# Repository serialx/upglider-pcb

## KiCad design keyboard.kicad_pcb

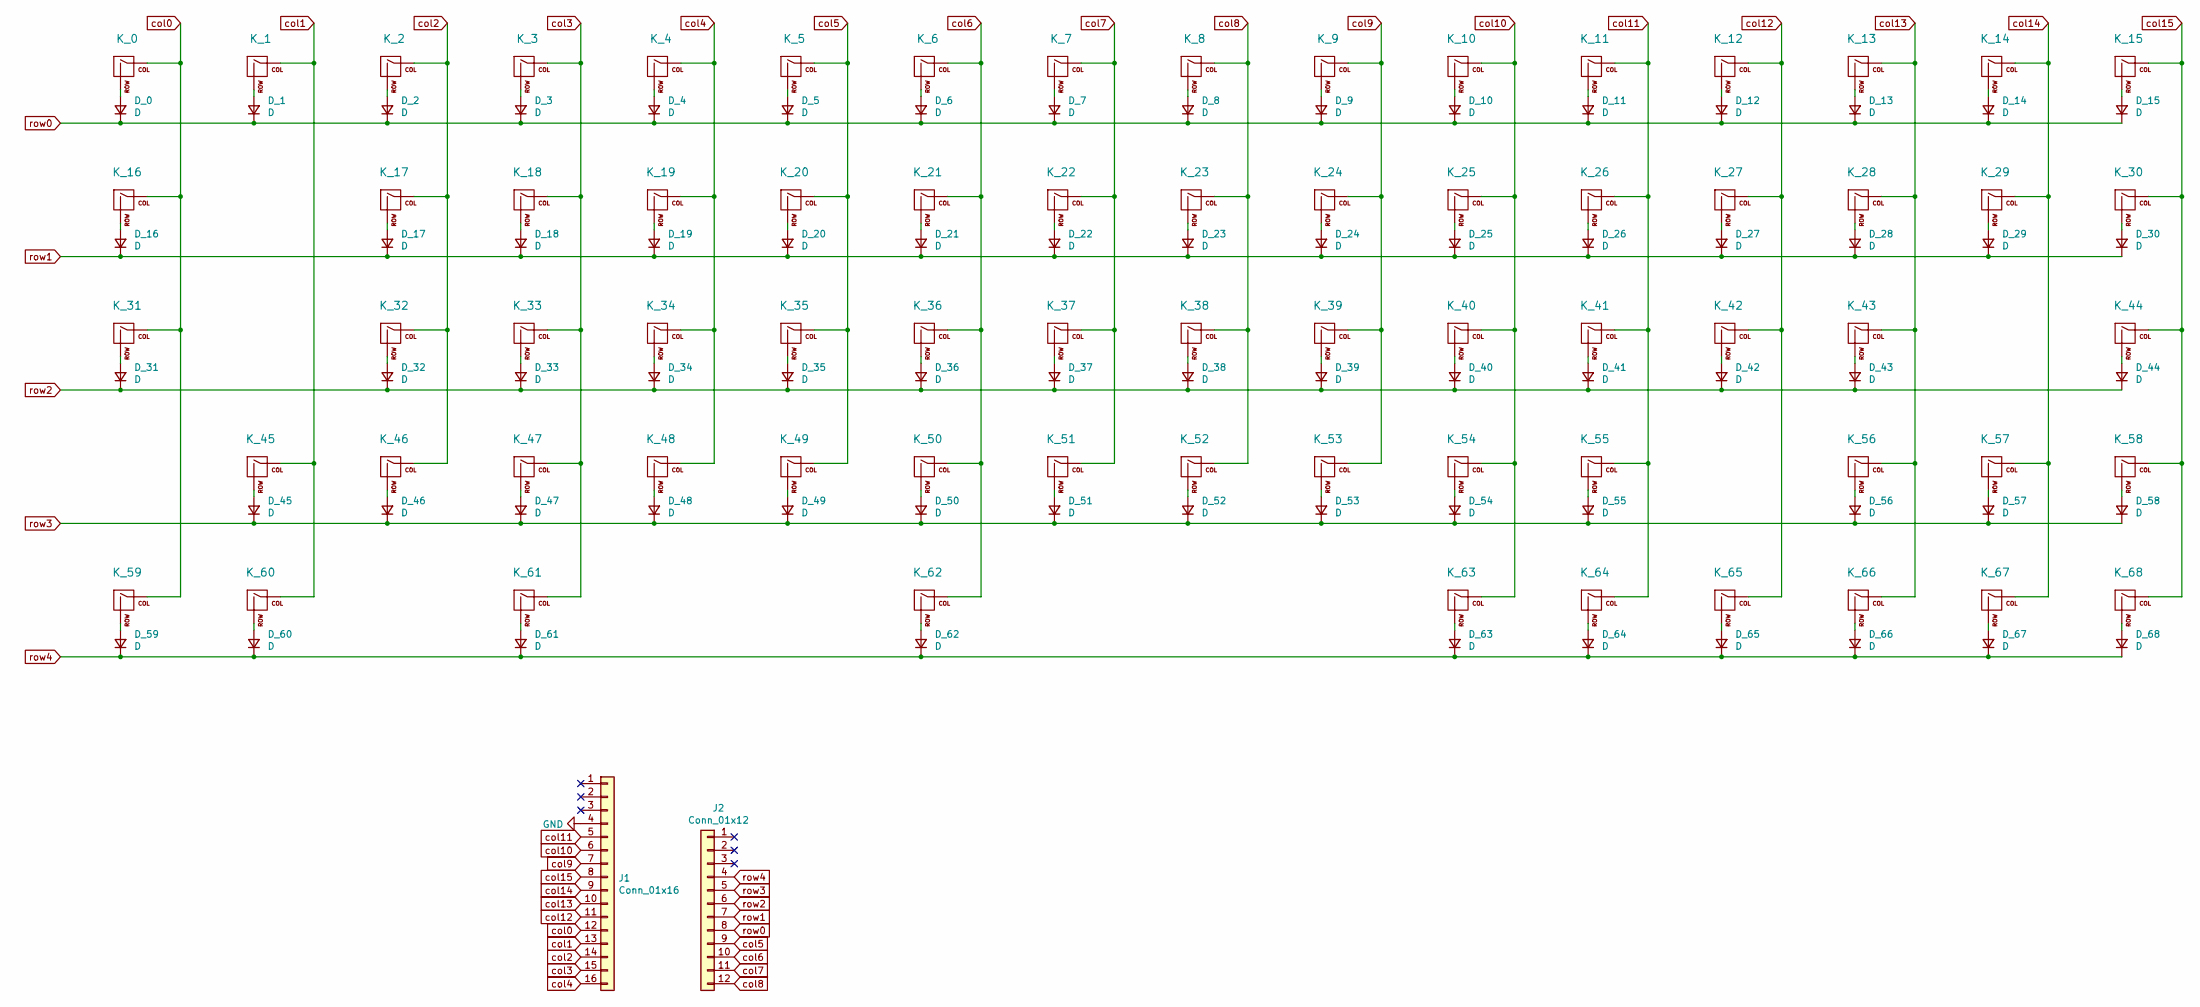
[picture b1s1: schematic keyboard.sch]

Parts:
D_0, D_1, D_2, D_3, D_4, D_5, D_6, D_7, D_8, D_9, D_10, D_11, D_12, D_13, D_14, D_15, D_16, D_17, D_18, D_19, D_20, D_21, D_22, D_23, D_24, D_25, D_26, D_27, D_28, D_29, D_30, D_31, D_32, D_33, D_34, D_35, D_36, D_37, D_38, D_39, D_40, D_41, D_42, D_43, D_44, D_45, D_46, D_47, D_48, D_49, D_50, D_51, D_52, D_53, D_54, D_55, D_56, D_57, D_58, D_59, D_60, D_61, D_62, D_63, D_64, D_65, D_66, D_67, D_68: D; D_SOD-123; LCSC Part # C81598
J1: Conn_01x16; PinSocket_1x16_P2.54mm_Vertical
J2: Conn_01x12; PinSocket_1x12_P2.54mm_Vertical
K_0, K_1, K_2, K_3, K_4, K_5, K_6, K_7, K_8, K_9, K_10, K_11, K_12, K_13, K_14, K_15, K_17, K_18, K_19, K_20, K_21, K_22, K_23, K_24, K_25, K_26, K_27, K_28, K_30, K_32, K_33, K_34, K_35, K_36, K_37, K_38, K_39, K_40, K_41, K_42, K_44, K_46, K_47, K_48, K_49, K_50, K_51, K_52, K_53, K_54, K_55, K_57, K_58, K_63, K_64, K_65, K_66, K_67, K_68: KEYSW; MXOnly-1U-Hotswap
K_16, K_29: KEYSW; MXOnly-1.5U-Hotswap
K_31, K_56: KEYSW; MXOnly-1.75U-Hotswap
K_43, K_45: KEYSW; MXOnly-2.25U-Hotswap
K_59, K_60, K_61: KEYSW; MXOnly-1.25U-Hotswap
K_62: KEYSW; MXOnly-6.25U-Hotswap

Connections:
GND: J1.4
unnamed: D_0.2 (A), K_0.2 (ROW)
unnamed: D_1.2 (A), K_1.2 (ROW)
unnamed: D_2.2 (A), K_2.2 (ROW)
unnamed: D_3.2 (A), K_3.2 (ROW)
unnamed: D_4.2 (A), K_4.2 (ROW)
unnamed: D_5.2 (A), K_5.2 (ROW)
unnamed: D_6.2 (A), K_6.2 (ROW)
unnamed: D_7.2 (A), K_7.2 (ROW)
unnamed: D_8.2 (A), K_8.2 (ROW)
unnamed: D_9.2 (A), K_9.2 (ROW)
unnamed: D_10.2 (A), K_10.2 (ROW)
unnamed: D_11.2 (A), K_11.2 (ROW)
unnamed: D_12.2 (A), K_12.2 (ROW)
unnamed: D_13.2 (A), K_13.2 (ROW)
unnamed: D_14.2 (A), K_14.2 (ROW)
unnamed: D_15.2 (A), K_15.2 (ROW)
unnamed: D_16.2 (A), K_16.2 (ROW)
unnamed: D_17.2 (A), K_17.2 (ROW)
unnamed: D_18.2 (A), K_18.2 (ROW)
unnamed: D_19.2 (A), K_19.2 (ROW)
unnamed: D_20.2 (A), K_20.2 (ROW)
unnamed: D_21.2 (A), K_21.2 (ROW)
unnamed: D_22.2 (A), K_22.2 (ROW)
unnamed: D_23.2 (A), K_23.2 (ROW)
unnamed: D_24.2 (A), K_24.2 (ROW)
unnamed: D_25.2 (A), K_25.2 (ROW)
unnamed: D_26.2 (A), K_26.2 (ROW)
unnamed: D_27.2 (A), K_27.2 (ROW)
unnamed: D_28.2 (A), K_28.2 (ROW)
unnamed: D_29.2 (A), K_29.2 (ROW)
unnamed: D_30.2 (A), K_30.2 (ROW)
unnamed: D_31.2 (A), K_31.2 (ROW)
unnamed: D_32.2 (A), K_32.2 (ROW)
unnamed: D_33.2 (A), K_33.2 (ROW)
unnamed: D_34.2 (A), K_34.2 (ROW)
unnamed: D_35.2 (A), K_35.2 (ROW)
unnamed: D_36.2 (A), K_36.2 (ROW)
unnamed: D_37.2 (A), K_37.2 (ROW)
unnamed: D_38.2 (A), K_38.2 (ROW)
unnamed: D_39.2 (A), K_39.2 (ROW)
unnamed: D_40.2 (A), K_40.2 (ROW)
unnamed: D_41.2 (A), K_41.2 (ROW)
unnamed: D_42.2 (A), K_42.2 (ROW)
unnamed: D_43.2 (A), K_43.2 (ROW)
unnamed: D_44.2 (A), K_44.2 (ROW)
unnamed: D_45.2 (A), K_45.2 (ROW)
unnamed: D_46.2 (A), K_46.2 (ROW)
unnamed: D_47.2 (A), K_47.2 (ROW)
unnamed: D_48.2 (A), K_48.2 (ROW)
unnamed: D_49.2 (A), K_49.2 (ROW)
unnamed: D_50.2 (A), K_50.2 (ROW)
unnamed: D_51.2 (A), K_51.2 (ROW)
unnamed: D_52.2 (A), K_52.2 (ROW)
unnamed: D_53.2 (A), K_53.2 (ROW)
unnamed: D_54.2 (A), K_54.2 (ROW)
unnamed: D_55.2 (A), K_55.2 (ROW)
unnamed: D_56.2 (A), K_56.2 (ROW)
unnamed: D_57.2 (A), K_57.2 (ROW)
unnamed: D_58.2 (A), K_58.2 (ROW)
unnamed: D_59.2 (A), K_59.2 (ROW)
unnamed: D_60.2 (A), K_60.2 (ROW)
unnamed: D_61.2 (A), K_61.2 (ROW)
unnamed: D_62.2 (A), K_62.2 (ROW)
unnamed: D_63.2 (A), K_63.2 (ROW)
unnamed: D_64.2 (A), K_64.2 (ROW)
unnamed: D_65.2 (A), K_65.2 (ROW)
unnamed: D_66.2 (A), K_66.2 (ROW)
unnamed: D_67.2 (A), K_67.2 (ROW)
unnamed: D_68.2 (A), K_68.2 (ROW)
col0: J1.12, K_0.1 (COL), K_16.1 (COL), K_31.1 (COL), K_59.1 (COL)
col1: J1.13, K_1.1 (COL), K_45.1 (COL), K_60.1 (COL)
col2: J1.14, K_2.1 (COL), K_17.1 (COL), K_32.1 (COL), K_46.1 (COL)
col3: J1.15, K_3.1 (COL), K_18.1 (COL), K_33.1 (COL), K_47.1 (COL), K_61.1 (COL)
col4: J1.16, K_4.1 (COL), K_19.1 (COL), K_34.1 (COL), K_48.1 (COL)
col5: J2.9, K_5.1 (COL), K_20.1 (COL), K_35.1 (COL), K_49.1 (COL)
col6: J2.10, K_6.1 (COL), K_21.1 (COL), K_36.1 (COL), K_50.1 (COL), K_62.1 (COL)
col7: J2.11, K_7.1 (COL), K_22.1 (COL), K_37.1 (COL), K_51.1 (COL)
col8: J2.12, K_8.1 (COL), K_23.1 (COL), K_38.1 (COL), K_52.1 (COL)
col9: J1.7, K_9.1 (COL), K_24.1 (COL), K_39.1 (COL), K_53.1 (COL)
col10: J1.6, K_10.1 (COL), K_25.1 (COL), K_40.1 (COL), K_54.1 (COL), K_63.1 (COL)
col11: J1.5, K_11.1 (COL), K_26.1 (COL), K_41.1 (COL), K_55.1 (COL), K_64.1 (COL)
col12: J1.11, K_12.1 (COL), K_27.1 (COL), K_42.1 (COL), K_65.1 (COL)
col13: J1.10, K_13.1 (COL), K_28.1 (COL), K_43.1 (COL), K_56.1 (COL), K_66.1 (COL)
col14: J1.9, K_14.1 (COL), K_29.1 (COL), K_57.1 (COL), K_67.1 (COL)
col15: J1.8, K_15.1 (COL), K_30.1 (COL), K_44.1 (COL), K_58.1 (COL), K_68.1 (COL)
row0: D_0.1 (K), D_1.1 (K), D_2.1 (K), D_3.1 (K), D_4.1 (K), D_5.1 (K), D_6.1 (K), D_7.1 (K), D_8.1 (K), D_9.1 (K), D_10.1 (K), D_11.1 (K), D_12.1 (K), D_13.1 (K), D_14.1 (K), D_15.1 (K), J2.8
row1: D_16.1 (K), D_17.1 (K), D_18.1 (K), D_19.1 (K), D_20.1 (K), D_21.1 (K), D_22.1 (K), D_23.1 (K), D_24.1 (K), D_25.1 (K), D_26.1 (K), D_27.1 (K), D_28.1 (K), D_29.1 (K), D_30.1 (K), J2.7
row2: D_31.1 (K), D_32.1 (K), D_33.1 (K), D_34.1 (K), D_35.1 (K), D_36.1 (K), D_37.1 (K), D_38.1 (K), D_39.1 (K), D_40.1 (K), D_41.1 (K), D_42.1 (K), D_43.1 (K), D_44.1 (K), J2.6
row3: D_45.1 (K), D_46.1 (K), D_47.1 (K), D_48.1 (K), D_49.1 (K), D_50.1 (K), D_51.1 (K), D_52.1 (K), D_53.1 (K), D_54.1 (K), D_55.1 (K), D_56.1 (K), D_57.1 (K), D_58.1 (K), J2.5
row4: D_59.1 (K), D_60.1 (K), D_61.1 (K), D_62.1 (K), D_63.1 (K), D_64.1 (K), D_65.1 (K), D_66.1 (K), D_67.1 (K), D_68.1 (K), J2.4

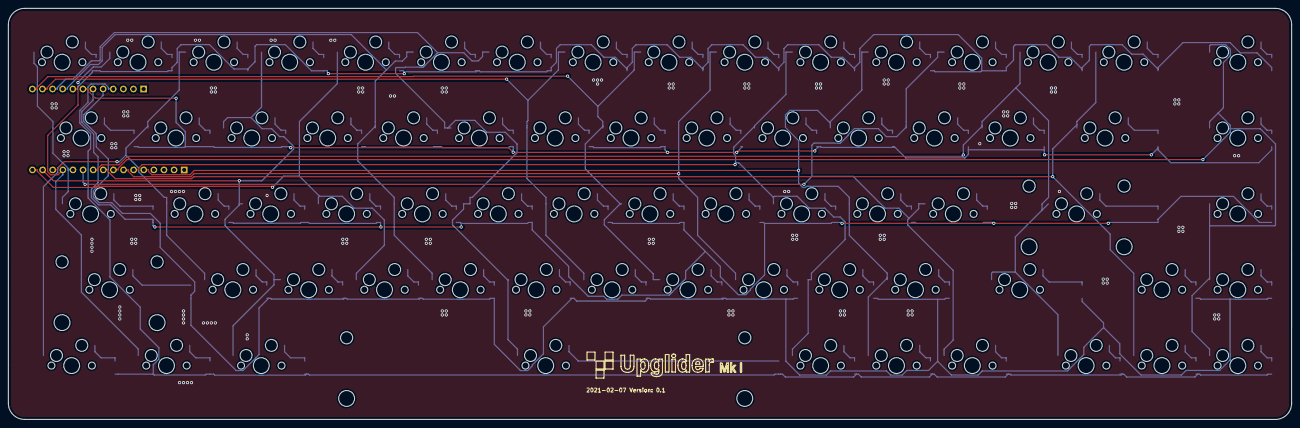
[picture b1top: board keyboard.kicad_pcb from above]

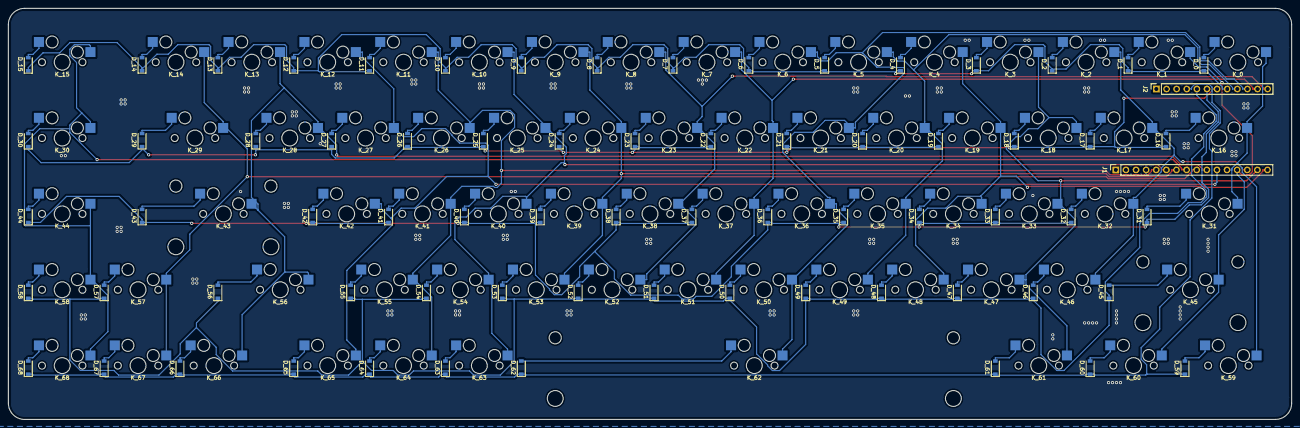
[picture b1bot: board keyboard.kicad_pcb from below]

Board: 2 copper layers, 322.3 x 103.2 mm, 140 parts (71 on the bottom side), 90 nets.

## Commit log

2021-01-24 Initial commit. First PCB prototype.
2021-01-24 Add nrfmicro footprints
2021-02-06 Add Adafruit feather wing socket. Version 0.1
2021-02-08 Add logo files
